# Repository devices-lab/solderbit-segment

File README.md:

# solder:bit Segment

The solder:bit Segment is a kit for learning to solder with surface-mount (SMT) components. When assembled, the device can display a single digit on a 7-segment display. It works with any microcontroller that communicates over the [I²C protocol](https://en.wikipedia.org/wiki/I2C).

This soldering kit is designed to accommodate a wide range of soldering abilities. The I/O expander is available in two different packages. The PCF8574AT in the **SO-16** package is smaller and more challenging to solder, while the PCF8574N in the **DIP-16** package is larger and through-hole (THT), making it more accessible for novices. The same printed circuit board (PCB) has footprints for both packages, and you choose which component to solder based on your ability. The device functions identically regardless of which package you use. Note that once you have soldered one package, the footprint for the other will no longer be accessible.

| I/O expander in an SO-16 package (SMT) | I/O expander in a DIP-16 package (THT) |
| -------------------------------------- | -------------------------------------- |
|            |           |

## Getting started

> [!WARNING]
> This device is a research prototype and is provided as-is. Use it at your own risk. The authors take no responsibility for any damage, injury, or loss arising from its use.

To get started, you will need the following:

1. The printed circuit boards (PCBs), which you will need to have manufactured.
2. All components listed in the bill of materials (BOM).
3. A microcontroller development board, like the BBC micro:bit.
4. All equipment and materials required for soldering.

### Printed circuit boards (PCBs)

The solder:bit Segment fabrication files are open source, so you can order the PCBs yourself!

To fabricate the PCB, use the files in the [gerbers-v0.1](/fabrication/gerbers-v0.1/) folder.

### Components

> [!NOTE]
> Most of these components are sourced from [Onecall (Farnell/CPC)](https://onecall.farnell.com/), but as they are fairly common components, alternatives can be found from other suppliers such as LCSC, DigiKey, and others.

| Reference | Quantity | Part            | Package     | Onecall order code |
| --------- | -------- | --------------- | ----------- | ------------------ |
| C1        | 1        | 1 µF \*         | 1206        | 3188966            |
| DS1       | 1        | VDMO10A0        | SMD, 10mm   | 2682705            |
| J1        | 1        | 5-pin header \* | 2.54mm, THT | 3049532            |
| R1–R8     | 8        | 150 Ω \*        | 1206        | 9240420            |
| U1        | 1        | PCF8574AT       | SO-16       | 2776146            |
| U2        | 1        | PCF8574N        | DIP-16      | 3124747            |

_\* Generic component; the order code is provided as a reference, but any equivalent component in the same package can be substituted._

Note that U1 and U2 are alternative packages for the same PCF8574 component — you only need one. You can source both and choose whichever you are more comfortable soldering.

The 7-segment display listed above has orange segments. If you would like other colours, Vishay also offers VDMR10A0 (red) and VDMG10A0 (green). Note that you might need to adjust R1-R8 resistor values to ensure the sinking current doesn't exceed 10 mA on each GPIO pin.

Depending on how you plan to connect the solder:bit Segment to your microcontroller development board, you may also need a breadboard and some jumper cables.

### Development board

You can use a BBC micro:bit to control the solder:bit Segment. Once assembled, attach the device to a breadboard, plug the micro:bit into a [breadboard adaptor](https://kitronik.co.uk/products/5664-microbit-breadboard-breakout-board), and connect it to the breadboard. See the [programming](#programming) section below to see how to wire it up.

> [!CAUTION]
> The device works at a supply voltage (VDD) from 2.5 V to 6 V.

The solder:bit Segment can also be used with other microcontroller development boards such as the [Raspberry Pi Pico](https://www.raspberrypi.com/products/raspberry-pi-pico/) or [Arduino Uno](https://store.arduino.cc/products/arduino-uno-rev3), however we currently only provide programming support for the micro:bit.

See the [programming](#programming) section below for how to write code to control the solder:bit Segment.

### Equipment and materials for soldering

The required equipment will vary depending on your soldering setup and needs, but the following is what you will generally need:

- Safety goggles
- Fume extractor fan
- Soldering iron
- Soldering iron stand
- Brass wool
- Silicone mat
- Solder
- Tweezers
- Solder wick

The following items are optional but useful:

- Blue Tack (for keeping the PCB in place)
- PCB holder/helping hands
- Flux
- Tip cleaner
- Desoldering pump
- Isopropyl alcohol (IPA) and cotton swabs
- Multimeter (for checking continuity in solder joints)

> [!CAUTION]
> To minimise health hazards, we recommend using lead-free and rosin-free solder and flux.

> [!TIP]
> If you are running this as a workshop/event activity, an [HDMI digital microscope](https://www.amazon.co.uk/dp/B09VPPS96M) connected to a display is very useful for streaming a soldering demonstration to the entire room.

> [!TIP]
> Smaller soldering iron tips make it easier to reach tight spaces, but they transfer heat less effectively. We recommend trying out a few different tip sizes and choosing one that works well with your soldering iron.

## Assembly instructions

Coming soon...

## Programming

If you are using a BBC micro:bit, you can program the solder:bit Segment in [MakeCode](https://makecode.microbit.org/) using the [pxt-solderbit-segment](https://github.com/devices-lab/pxt-solderbit-segment) extension.

You can test if your assembled device works by flashing the micro:bit with the [demo file](/demo/microbit-solderbit-segment-demo.hex). Attach the solder:bit Segment to a breadboard, insert the micro:bit into a [breadboard adaptor](https://kitronik.co.uk/products/5664-microbit-breadboard-breakout-board), and plug it into the breadboard. Connect the device to the micro:bit using the following pinout:

| solder:bit Segment | BBC micro:bit |
| ------------------ | ------------- |
| GND                | GND           |
| VDD                | 3V            |
| SDA                | P20           |
| SCL                | P19           |

See [this image](/demo/wiring_front.jpeg) and [this image](/demo/wiring_back.jpeg) for an example of how to wire it up.

For any other development board, you will need to write the firmware yourself. Refer to the [solder:bit Segment schematic](/reference/solderbit%20Segment%20v0.1%20schematic.pdf), the datasheets for the I/O expanders (both packages), and the 7-segment display datasheet, all of which are available in the [reference](/reference/) folder.

> [!WARNING]
> The two I/O expander packages have different I²C addresses. With the current PCB layout and configuration, the PCF8574AT (SO-16 package) has an I²C address of `0x38`, while the PCF8574N (DIP-16 package) has an address of `0x20`. When writing your own firmware, make sure you are using the correct address for the package you have soldered. The [pxt-solderbit-segment](https://github.com/devices-lab/pxt-solderbit-segment) MakeCode extension handles this for you.

## Project status and contributing

This project is actively maintained. See [CHANGELOG.md](/CHANGELOG.md) for the latest changes.

At this time, external contributions are not being accepted. If you have suggestions or have found an issue, feel free to open a GitHub issue and we will take a look.

## Contact

If you are interested in using solder:bit kits for your classroom, university, conference, or any other workshop or event, feel free to reach out to me @mac-aron or contact [Devices Lab](https://devices-lab.org/contact).

## Acknowledgements

Special thanks to everyone at the [Devices Lab](https://www.devices-lab.org/) for their ongoing support on this project and for their help running soldering workshops.

## License

This project is licensed under the GNU General Public License (GPL), version 3. This license allows you to use, modify, and redistribute the solder:bit Segment and any derivative works, but all such derivatives must also be licensed under the GPL.

The GPL ensures that all modifications and improvements to the solder:bit Segment remain free and open for the public benefit. By using this project, you agree to abide by its terms and conditions.

For more details on the license, please see the [LICENSE](/LICENSE) file included in this repository.

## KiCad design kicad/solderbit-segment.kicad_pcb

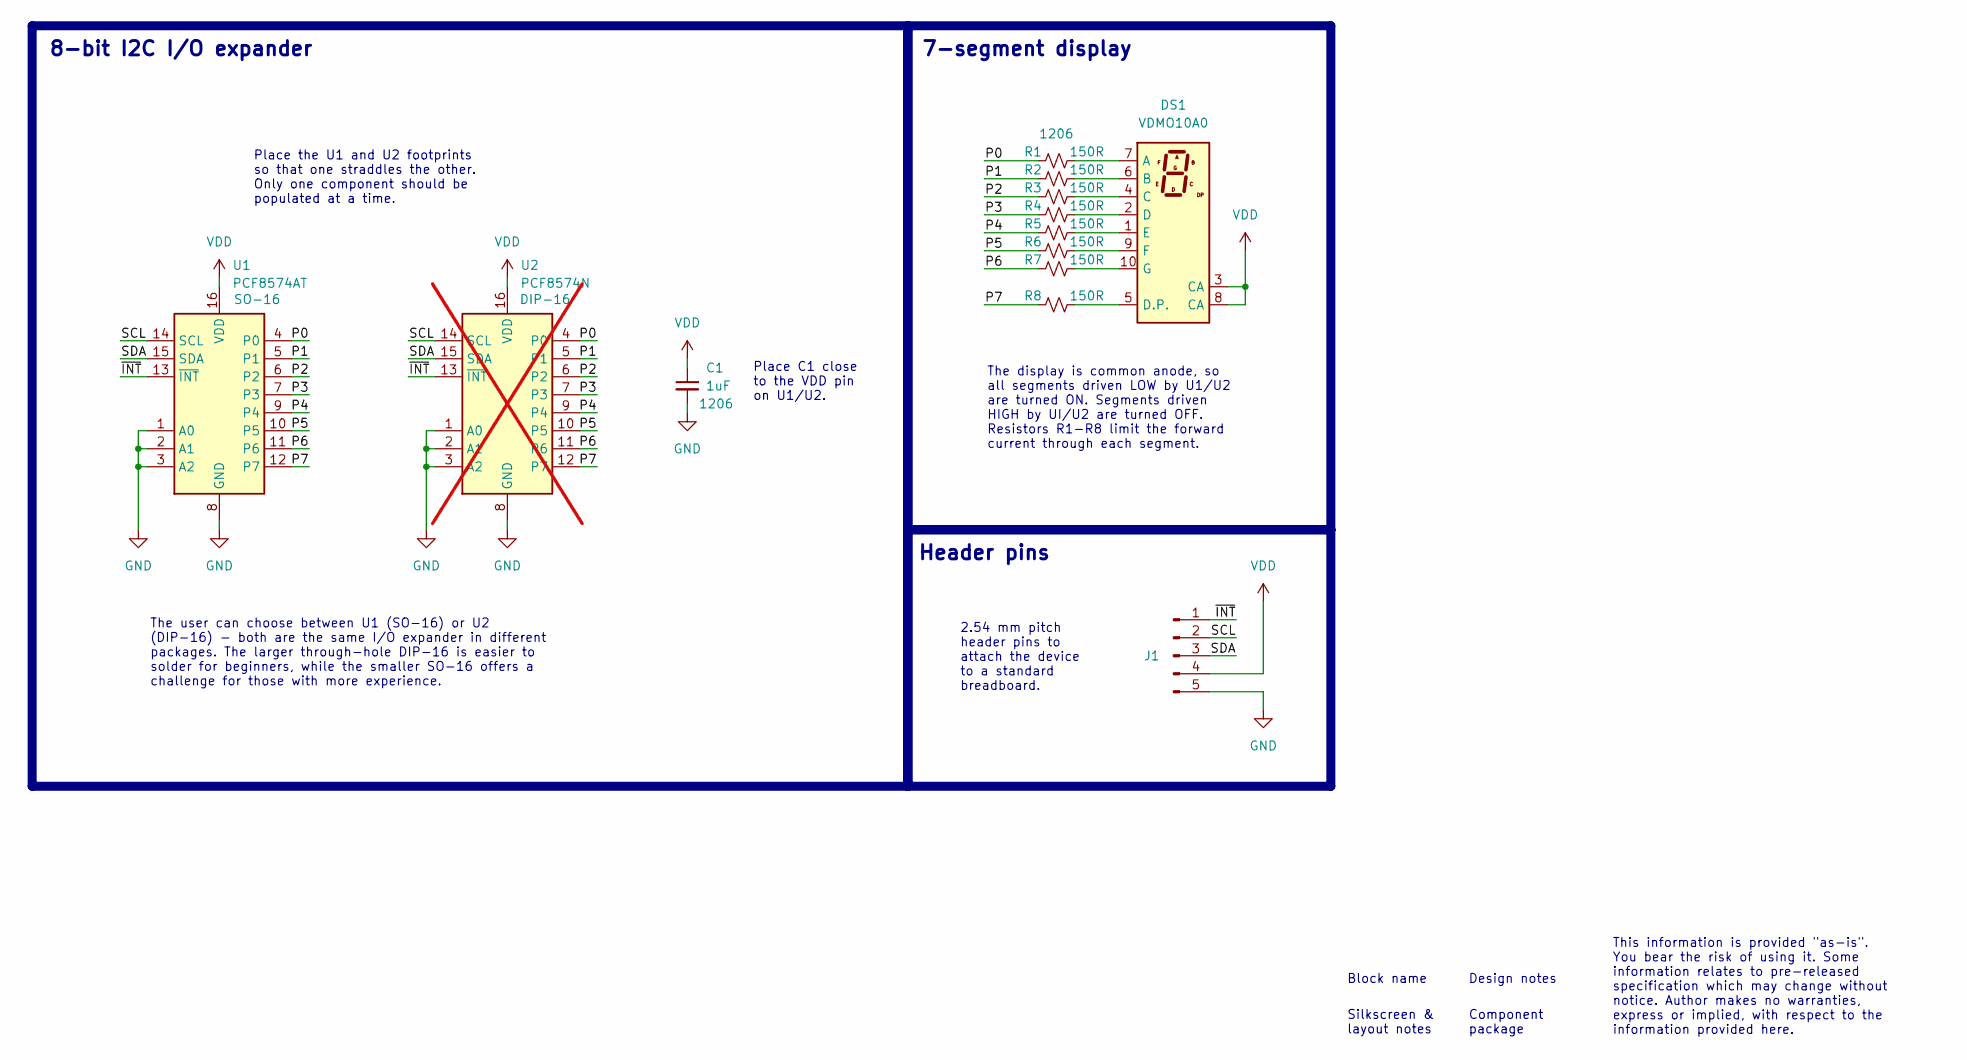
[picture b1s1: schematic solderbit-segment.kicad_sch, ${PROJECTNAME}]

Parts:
C1: 1uF; C_1206
DS1: VDMO10A0; VDMR10; LCSC Part C2913076
J1: Conn_01x05_Pin; PinHeader_1x05_P2.54mm_Vertical
R1, R2, R3, R4, R5, R6, R7, R8: 150R; R_1206
U1: PCF8574AT; SO-16
U2: PCF8574N; DIP-16; not fitted

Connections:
/P0: R1.1, U1.4 (P0), U2.4 (P0)
/P1: R2.1, U1.5 (P1), U2.5 (P1)
/P2: R3.1, U1.6 (P2), U2.6 (P2)
/P3: R4.1, U1.7 (P3), U2.7 (P3)
/P4: R5.1, U1.9 (P4), U2.9 (P4)
/P5: R6.1, U1.10 (P5), U2.10 (P5)
/P6: R7.1, U1.11 (P6), U2.11 (P6)
/P7: R8.1, U1.12 (P7), U2.12 (P7)
/SCL: J1.2, U1.14 (SCL), U2.14 (SCL)
/SDA: J1.3, U1.15 (SDA), U2.15 (SDA)
/~INT: J1.1, U1.13 (~INT), U2.13 (~INT)
GND: C1.2, J1.5, U1.1 (A0), U1.2 (A1), U1.3 (A2), U1.8 (GND), U2.1 (A0), U2.2 (A1), U2.3 (A2), U2.8 (GND)
unnamed: DS1.7 (A), R1.2
unnamed: DS1.6 (B), R2.2
unnamed: DS1.4 (C), R3.2
unnamed: DS1.2 (D), R4.2
unnamed: DS1.5 (D.P.), R8.2
unnamed: DS1.1 (E), R5.2
unnamed: DS1.9 (F), R6.2
unnamed: DS1.10 (G), R7.2
VDD: C1.1, DS1.3 (CA), DS1.8 (CA), J1.4, U1.16 (VDD), U2.16 (VDD)

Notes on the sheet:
The user can choose between U1 (SO-16) or U2 (DIP-16) - both are the same I/O expander in different packages. The larger through-hole DIP-16 is easier to solder for beginners, while the smaller SO-16 offers a challenge for those with more experience.
Silkscreen & layout notes
Component package
Place the U1 and U2 footprints so that one straddles the other. Only one component should be populated at a time.
2.54 mm pitch header pins to attach the device to a standard breadboard.
Header pins
Block name
This information is provided "as-is". You bear the risk of using it. Some information relates to pre-released specification which may change without notice. Author makes no warranties, express or implied, with respect to the information provided here.
The display is common anode, so all segments driven LOW by U1/U2 are turned ON. Segments driven HIGH by UI/U2 are turned OFF. Resistors R1-R8 limit the forward current through each segment.
Place C1 close to the VDD pin on U1/U2.
7-segment display
8-bit I2C I/O expander
Design notes

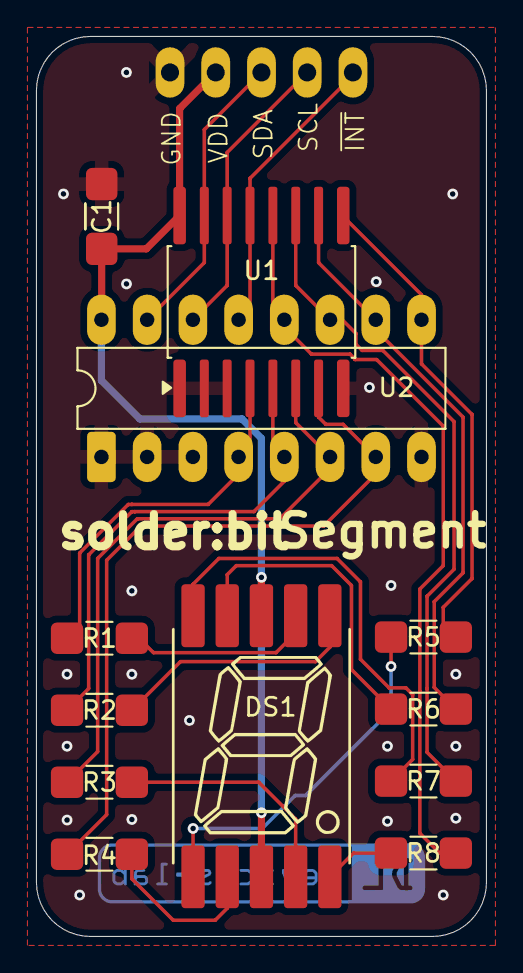
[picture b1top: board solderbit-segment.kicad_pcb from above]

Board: 2 copper layers, 25.0 x 50.0 mm, 13 parts (1 on the bottom side), 21 nets.

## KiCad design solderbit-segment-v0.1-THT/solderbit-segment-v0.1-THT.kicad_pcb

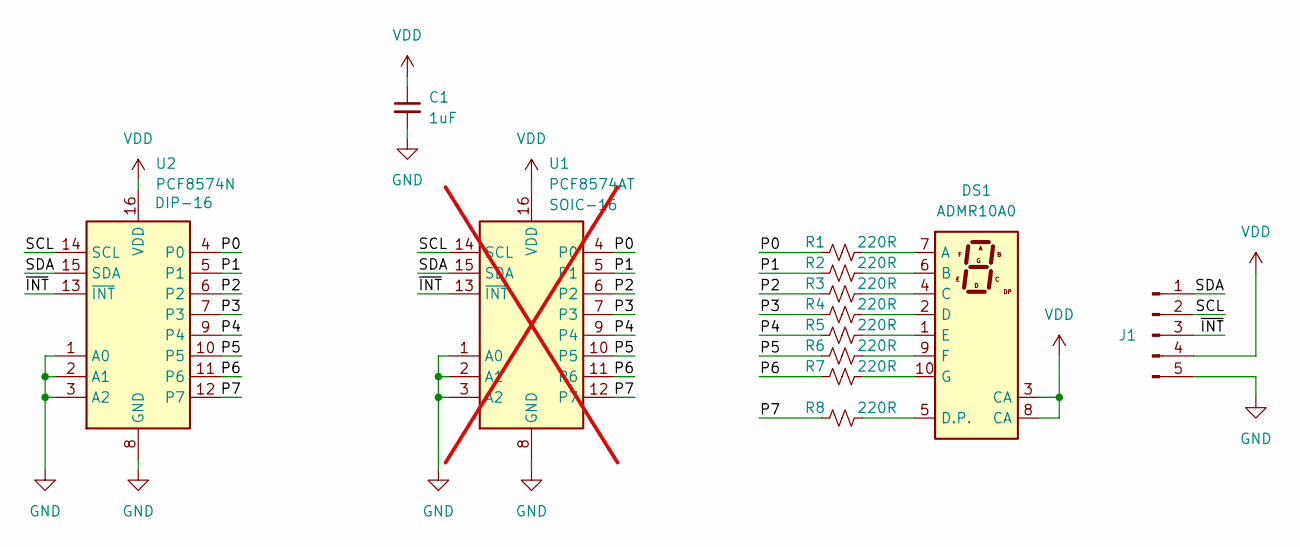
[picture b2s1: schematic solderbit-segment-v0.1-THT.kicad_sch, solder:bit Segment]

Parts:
C1: 1uF; C_1206
DS1: ADMR10A0; VDMR10
J1: Conn_01x05_Pin; PinHeader_1x05_P2.54mm_Vertical
R1, R2, R3, R4, R5, R6, R7, R8: 220R; R_1206
U1: PCF8574AT; SO-16; not fitted
U2: PCF8574N; DIP-16

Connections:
/P0: R1.1, U1.4 (P0), U2.4 (P0)
/P1: R2.1, U1.5 (P1), U2.5 (P1)
/P2: R3.1, U1.6 (P2), U2.6 (P2)
/P3: R4.1, U1.7 (P3), U2.7 (P3)
/P4: R5.1, U1.9 (P4), U2.9 (P4)
/P5: R6.1, U1.10 (P5), U2.10 (P5)
/P6: R7.1, U1.11 (P6), U2.11 (P6)
/P7: R8.1, U1.12 (P7), U2.12 (P7)
/SCL: J1.2, U1.14 (SCL), U2.14 (SCL)
/SDA: J1.1, U1.15 (SDA), U2.15 (SDA)
/~INT: J1.3, U1.13 (~INT), U2.13 (~INT)
GND: C1.2, J1.5, U1.1 (A0), U1.2 (A1), U1.3 (A2), U1.8 (GND), U2.1 (A0), U2.2 (A1), U2.3 (A2), U2.8 (GND)
unnamed: DS1.7 (A), R1.2
unnamed: DS1.6 (B), R2.2
unnamed: DS1.4 (C), R3.2
unnamed: DS1.2 (D), R4.2
unnamed: DS1.5 (D.P.), R8.2
unnamed: DS1.1 (E), R5.2
unnamed: DS1.9 (F), R6.2
unnamed: DS1.10 (G), R7.2
VDD: C1.1, DS1.3 (CA), DS1.8 (CA), J1.4, U1.16 (VDD), U2.16 (VDD)

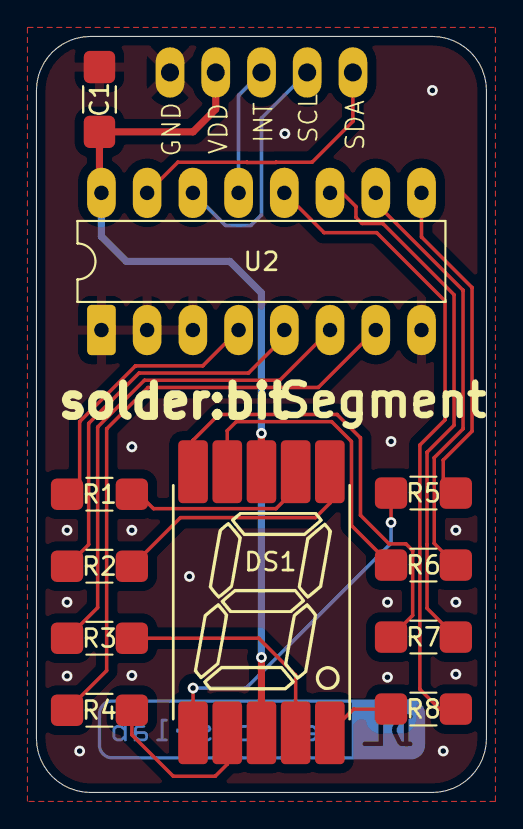
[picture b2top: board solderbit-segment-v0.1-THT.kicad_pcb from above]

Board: 2 copper layers, 25.0 x 42.0 mm, 12 parts (1 on the bottom side), 21 nets.

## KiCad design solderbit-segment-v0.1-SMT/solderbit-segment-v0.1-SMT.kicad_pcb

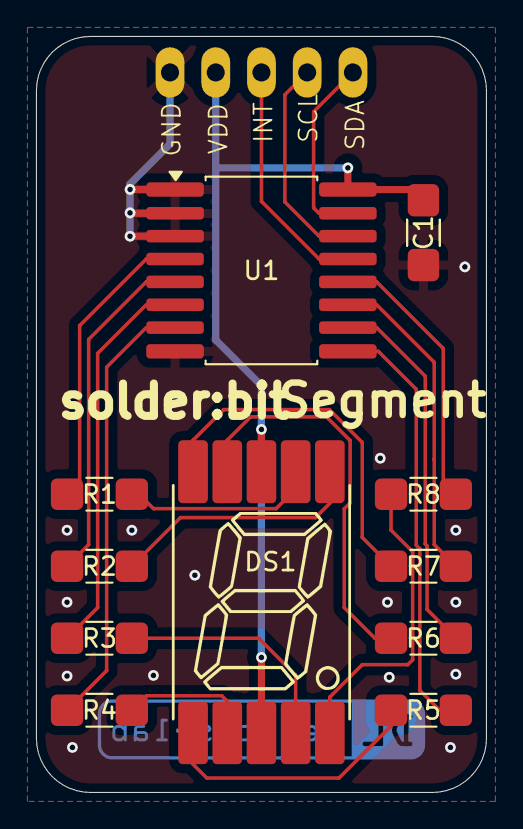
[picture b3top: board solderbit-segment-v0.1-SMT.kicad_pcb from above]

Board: 2 copper layers, 25.0 x 42.0 mm, 12 parts (1 on the bottom side), 21 nets.

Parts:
C1: C_Small; C_1206
DS1: ADMR10A0; VDMR10
J1: Conn_01x05_Pin; PinHeader_1x05_P2.54mm_Vertical
R1, R2, R3, R4, R5, R6, R7, R8: 220R; R_1206
U1: PCF8574AT; SO-16

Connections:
/P0: R1.1, U1.4 (P0)
/P1: R2.1, U1.5 (P1)
/P2: R3.1, U1.6 (P2)
/P3: R4.1, U1.7 (P3)
/P4: R5.1, U1.9 (P4)
/P5: R6.1, U1.10 (P5)
/P6: R7.1, U1.11 (P6)
/P7: R8.1, U1.12 (P7)
/SCL: J1.2, U1.14 (SCL)
/SDA: J1.1, U1.15 (SDA)
/~INT: J1.3, U1.13 (~INT)
GND: C1.2, J1.5, U1.1 (A0), U1.2 (A1), U1.3 (A2), U1.8 (GND)
unnamed: DS1.7 (A), R1.2
unnamed: DS1.6 (B), R2.2
unnamed: DS1.4 (C), R3.2
unnamed: DS1.2 (D), R4.2
unnamed: DS1.5 (D.P.), R8.2
unnamed: DS1.1 (E), R5.2
unnamed: DS1.9 (F), R6.2
unnamed: DS1.10 (G), R7.2
VDD: C1.1, DS1.3 (CA), DS1.8 (CA), J1.4, U1.16 (VDD)

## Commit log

2026-02-11 Second commit
2026-02-11 Separate SMT version, and THT I/O expander
2026-02-11 PCB with dual footprints
2026-02-11 Update README and generate some renders
2026-02-11 Deleted all KiCad backup files
2026-02-17 Update schematic and cleanup
2026-02-18 .gitignore update for pxt_modules & npm for firmware addition in subsequent commit
2026-02-18 added devices-lab/solderbit-segment-firmware as a submodule
2026-02-18 firmare: bumped to 0.0.2
2026-02-18 Add MakeCode extension details to README
    Added information about the MakeCode extension and its repository.
2026-02-18 Update README to reflect firmware repo privacy status
    Clarify the status of the firmware repository regarding its visibility for MakeCode extension import.
2026-02-18 firmare: bumped to 0.0.3
2026-02-18 firmare: bumped to 0.0.4
2026-02-18 firmware: bump to 0.05
2026-02-18 Fixed the 7-segment display part number
2026-02-18 Remove the extension submodule
2026-02-18 Removed initial experiments
2026-02-18 Make a copy to archive v0.1
2026-02-24 Repo cleanup and library links changes
2026-02-26 New documentation
2026-02-26 Update documentation
2026-02-26 Updated renders of the packages
2026-02-26 Cropped images
2026-02-26 Revert "Cropped images"
    This reverts commit 414280fbcbff03bf34e5a095220bf4c66dff73af.
2026-02-26 Added an image of the back to README
2026-04-21 New back image
2026-04-21 Update LICENSE file
2026-04-22 First save with KiCad 10
2026-04-22 Updated renders with green soldermask
